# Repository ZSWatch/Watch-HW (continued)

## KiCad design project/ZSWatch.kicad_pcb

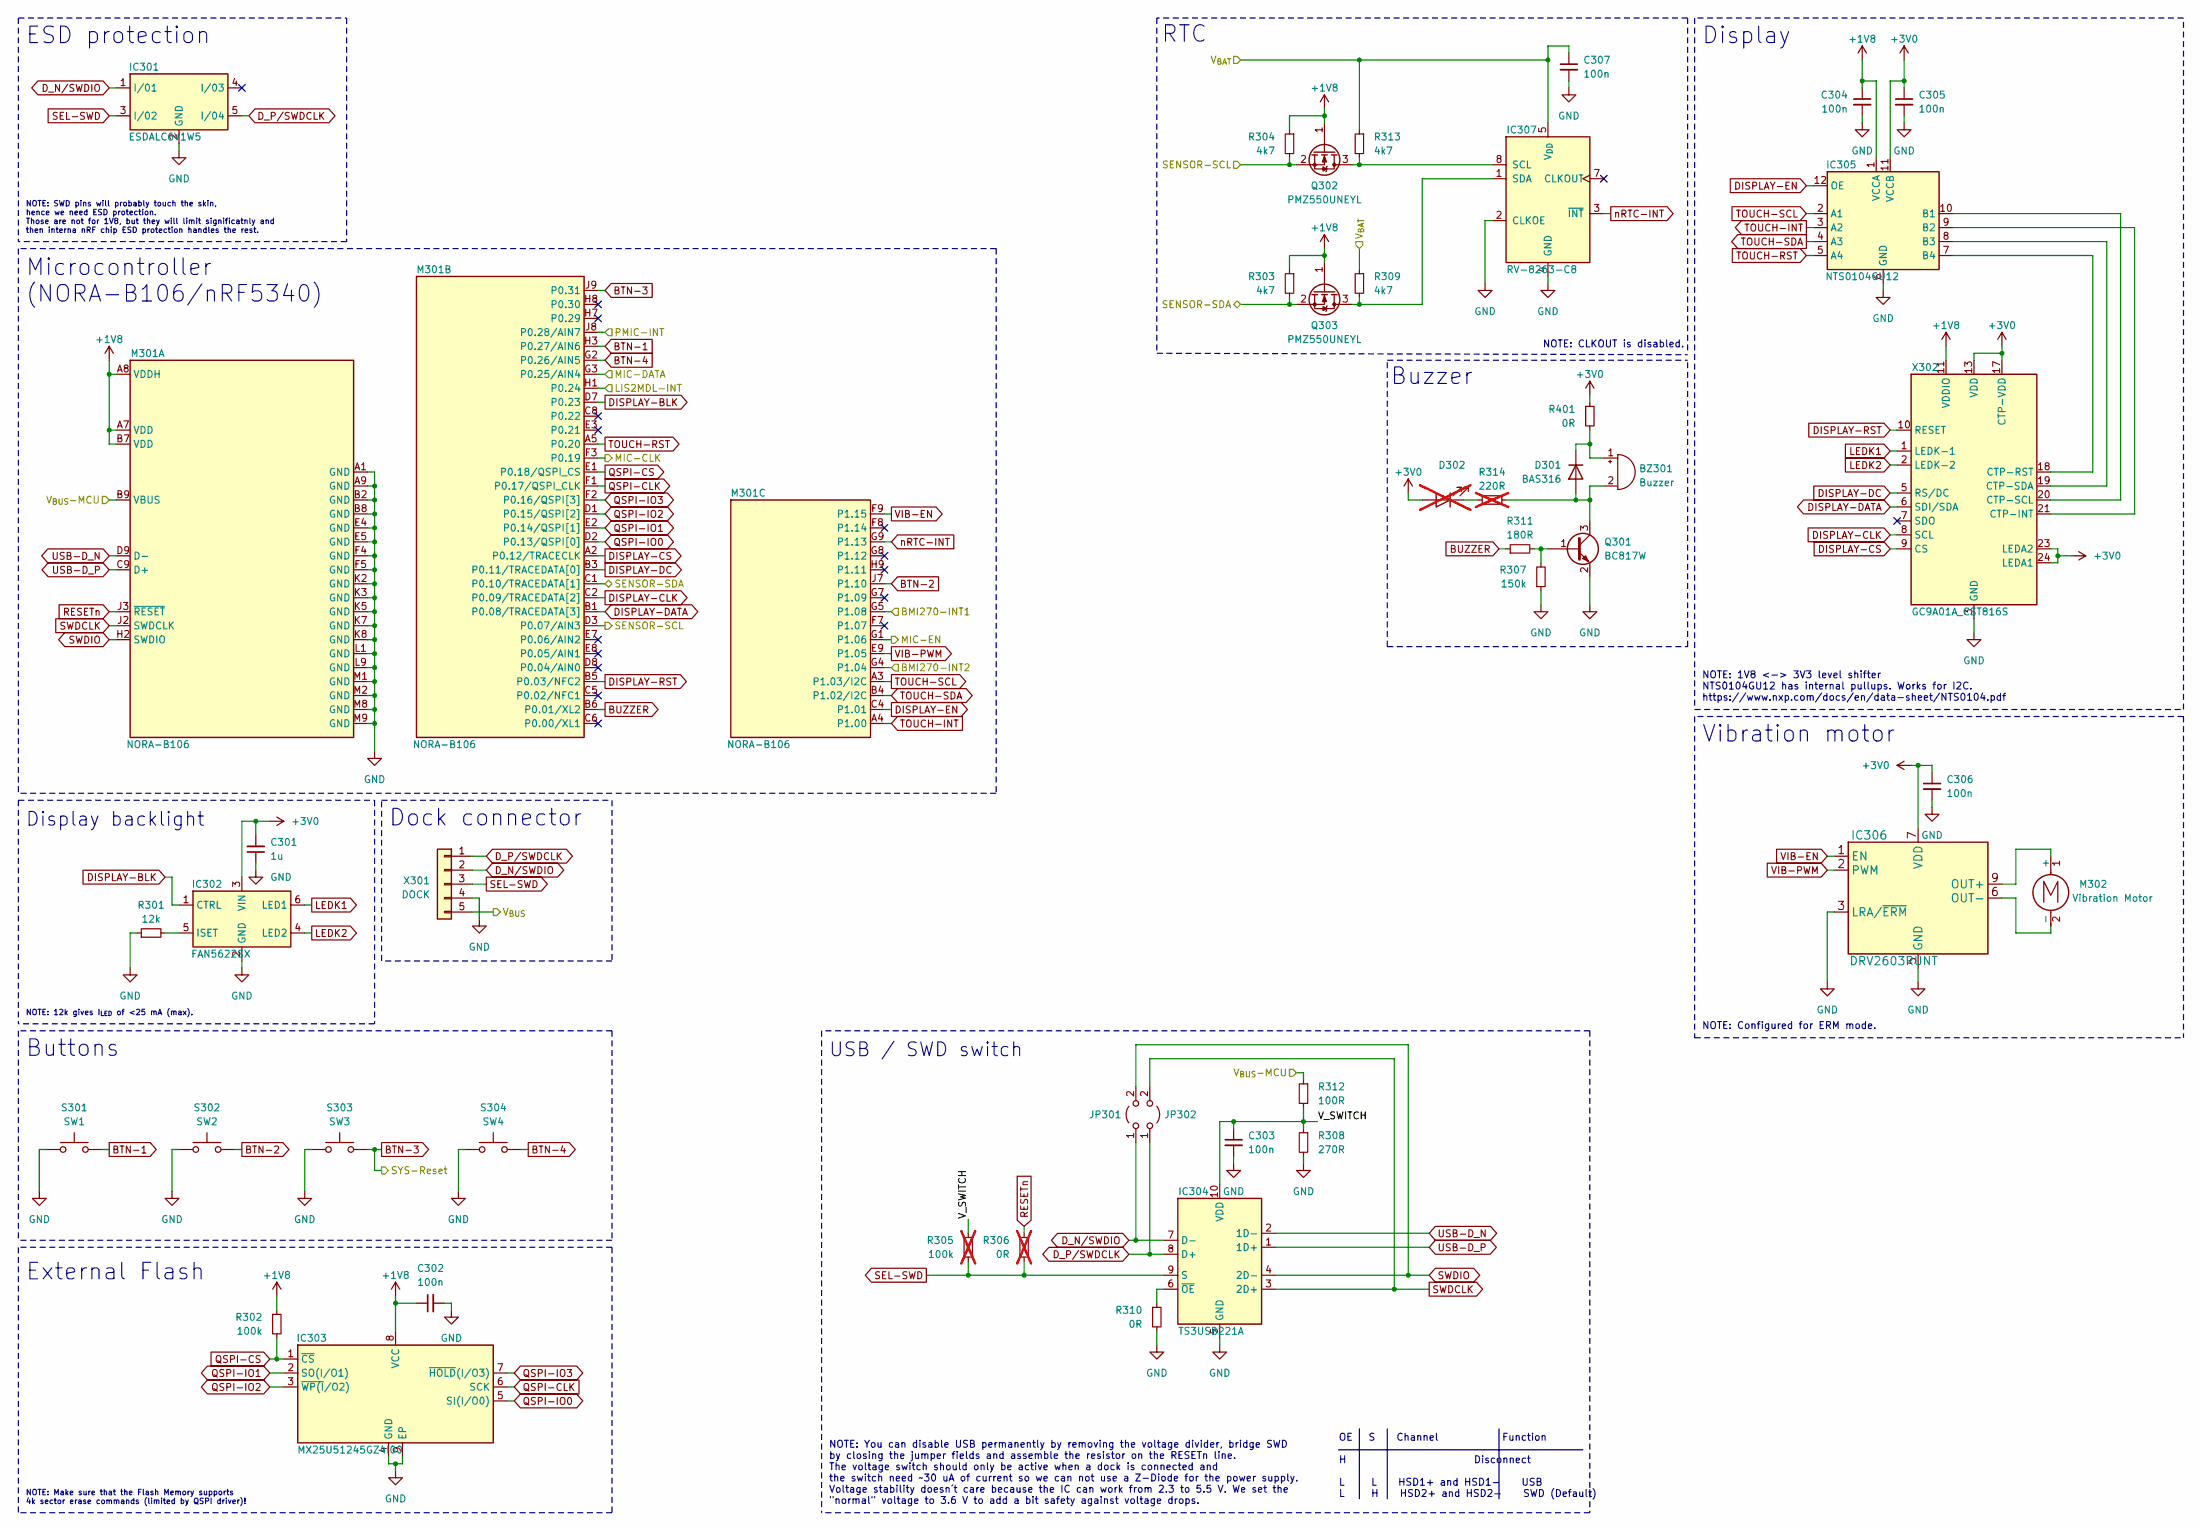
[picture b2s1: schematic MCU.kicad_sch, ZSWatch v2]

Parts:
BZ301: Buzzer; CMT-322-65-SMT-TR; mouser# 490-CMT-322-65-SMTTR
C301: 1u; C_0603_1608Metric; mouser# 581-0603YC105JAT2A
C302, C303, C304, C305, C306: 100n; C_0603_1608Metric; mouser# 581-06035C104KAT2A
C307: 100n; C_0402_1005Metric; mouser# 581-04025C104KAT2A
D301: BAS316; D_SOD-323; mouser# 821-BAS316RRG
D302: LED_0603_1608Metric; mouser# 710-150060YS75003; not fitted
IC301: ESDALC6V1W5; SOT-665; mouser# 511-ESDALC6V1P5
IC302: FAN5622SX; TSOT-23-6; mouser# 512-FAN5622SX
IC303: MX25U51245GZ4I00; WSON-8-1EP_8x6mm_P1.27mm_EP3.4x4.3mm; mouser# 95-25U51245GZ4I00T
IC304: TS3USB221A; UQFN-10_1.55x2.05mm_P0.5mm; mouser# 595-TS3USB221A
IC305: NTS0104GU12; XQFN-12-1.7x2mm_P0.4mm; mouser# 771-NTS0104GU12115
IC306: DRV2603RUNT; WQFN-10_2x2mm_P0.5mm; mouser# 595-DRV2603RUNT
IC307: RV-8263-C8; mouser# 428-204291-MC01
JP301, JP302: SolderJumper-2_P1.3mm_Open_RoundedPad1.0x1.5mm
M301: NORA-B106; mouser# 377-NORA-B106-00B
M302: Vibration Motor; VZ30C1T8219732L; mouser# 1670-VZ30C1T8219732LCT-ND
Q301: BC817W; SOT-323_SC-70; mouser# 771-BC817W115
Q302, Q303: PMZ550UNEYL; SOT-883; mouser# 771-PMZ550UNEYL
R301: 12k; R_0603_1608Metric; mouser# 603-RC0603FR-0712KL
R302: 100k; R_0603_1608Metric; mouser# 603-RC0603FR-07100KL
R303, R304: 4k7; R_0603_1608Metric; mouser# -- verschiedene Werte --
R305: 100k; R_0603_1608Metric; mouser# 603-RC0603FR-07100KL; not fitted
R306: 0R; R_0402_1005Metric; mouser# 652-CR0603-J/-000ELF; not fitted
R307: 150k; R_0603_1608Metric; mouser# 603-RC0603FR-07150KL
R308: 270R; R_0603_1608Metric; mouser# 603-RC0603FR-07270RL
R309, R313: 4k7; R_0402_1005Metric; mouser# -- verschiedene Werte --
R310: 0R; R_0402_1005Metric; mouser# 652-CR0603-J/-000ELF
R311: 180R; R_0603_1608Metric; mouser# 603-RC0603FR-07180RL
R312: 100R; R_0603_1608Metric; mouser# 603-RC0603FR-07100RL
R314: 220R; R_0603_1608Metric; mouser# 603-RT0603FRE07220RL; not fitted
R401: 0R; R_0603_1608Metric; mouser# 603-RC0603FR-100RL
S301: SW1; TL6340AF160Q_Modified; mouser# 612-TL6340AF160Q
S302: SW2; TL6340AF160Q_Modified; mouser# 612-TL6340AF160Q
S303: SW3; TL6340AF160Q_Modified; mouser# 612-TL6340AF160Q
S304: SW4; TL6340AF160Q_Modified; mouser# 612-TL6340AF160Q
X301: DOCK; RD90_LZH0230529-004_DJ-5PIN_PH2_54
X302: GC9A01A_CST816S; ER-CON0.4-24P

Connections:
+1V8: C302.1, C304.1, IC303.8 (VCC), IC305.1 (VCCA), M301.A7 (VDD), M301.A8 (VDDH), M301.B7 (VDD), Q302.1 (G), Q303.1 (G), R302.1, R303.1, R304.1, X302.11 (VDDIO), X302.12 (VDDIO); also elsewhere on the board
+3V0: C301.2, C305.1, C306.1, D302.2 (A), IC302.3 (VIN), IC305.11 (VCCB), IC306.7 (VDD), R401.1, X302.13 (VDD), X302.14 (VDD), X302.17 (CTP-VDD), X302.23 (LEDA2), X302.24 (LEDA1); also elsewhere on the board
/MCU/BMI270-INT1: M301.G5 (P1.08); also elsewhere on the board
/MCU/BMI270-INT2: M301.G4 (P1.04); also elsewhere on the board
/MCU/LIS2MDL-INT: M301.H1 (P0.24); also elsewhere on the board
/MCU/MIC-CLK: M301.F3 (P0.19); also elsewhere on the board
/MCU/MIC-DATA: M301.G3 (P0.25/AIN4); also elsewhere on the board
/MCU/MIC-EN: M301.G1 (P1.06); also elsewhere on the board
/MCU/PMIC-INT: M301.J8 (P0.28/AIN7); also elsewhere on the board
/MCU/SENSOR-SCL: M301.D3 (P0.07/AIN3), Q302.2 (S), R304.2; also elsewhere on the board
/MCU/SENSOR-SDA: M301.C1 (P0.10/TRACEDATA[1]), Q303.2 (S), R303.2; also elsewhere on the board
/MCU/V_SWITCH: C303.1, IC304.10 (VDD), R305.1, R308.1, R312.2
/MCU/V_{BAT}: C307.1, IC307.5 (V_{DD}), R309.1, R313.1; also elsewhere on the board
/MCU/V_{BUS}: X301.5; also elsewhere on the board
/MCU/V_{BUS}-MCU: M301.B9 (VBUS), R312.1; also elsewhere on the board
BTN-1: M301.H3 (P0.27/AIN6), S301.1
BTN-2: M301.J7 (P1.10), S302.2
BTN-3: M301.J9 (P0.31), S303.2; also elsewhere on the board
BTN-4: M301.G2 (P0.26/AIN5), S304.1
BUZZER: M301.B6 (P0.01/XL2), R311.1
DISPLAY-BLK: IC302.1 (CTRL), M301.D7 (P0.23)
DISPLAY-CLK: M301.C2 (P0.09/TRACEDATA[2]), X302.8 (SCL)
DISPLAY-CS: M301.A2 (P0.12/TRACECLK), X302.9 (CS)
DISPLAY-DATA: M301.B1 (P0.08/TRACEDATA[3]), X302.6 (SDI/SDA)
DISPLAY-DC: M301.B3 (P0.11/TRACEDATA[0]), X302.5 (RS/DC)
DISPLAY-EN: IC305.12 (OE), M301.C4 (P1.01)
DISPLAY-RST: M301.B5 (P0.03/NFC2), X302.10 (RESET)
D_N/SWDIO: IC301.1 (I/01), IC304.7 (D-), JP301.1 (A), X301.2
D_P/SWDCLK: IC301.5 (I/04), IC304.8 (D+), JP302.1 (A), X301.1
GND: C301.1, C302.2, C303.2, C304.2, C305.2, C306.2, C307.2, IC301.2 (GND), IC302.2 (GND), IC303.4 (GND), IC303.9 (EP), IC304.5 (GND), IC305.6 (GND), IC306.3 (LRA/~ERM), IC306.5 (GND), IC306.8 (GND), IC306.10 (GND), IC307.2 (CLKOE), IC307.4 (GND), M301.A1 (GND), M301.A9 (GND), M301.B2 (GND), M301.B8 (GND), M301.E4 (GND), M301.E5 (GND), M301.F4 (GND), M301.F5 (GND), M301.K2 (GND), M301.K3 (GND), M301.K5 (GND), M301.K7 (GND), M301.K8 (GND), M301.L1 (GND), M301.L9 (GND), M301.M1 (GND), M301.M2 (GND), M301.M8 (GND), M301.M9 (GND), Q301.2 (E), R301.1, R307.1, R308.2, R310.2, S301.2, S302.1, S303.1, S304.2, X301.4, X302.3 (GND), X302.4 (GND), X302.15 (GND), X302.16 (GND); also elsewhere on the board
LEDK1: IC302.6 (LED1), X302.1 (LEDK-1)
LEDK2: IC302.4 (LED2), X302.2 (LEDK-2)
unnamed: BZ301.1 (+), D301.1 (K), R401.2
unnamed: BZ301.2 (-), D301.2 (A), Q301.3 (C), R314.2
unnamed: D302.1 (K), R314.1
unnamed: IC302.5 (ISET), R301.2
unnamed: IC304.6 (~OE), R310.1
unnamed: IC305.10 (B1), X302.20 (CTP-SCL)
unnamed: IC305.9 (B2), X302.21 (CTP-INT)
unnamed: IC305.8 (B3), X302.19 (CTP-SDA)
unnamed: IC305.7 (B4), X302.18 (CTP-RST)
unnamed: IC306.9 (OUT+), M302.1 (+)
unnamed: IC306.6 (OUT-), M302.2 (-)
unnamed: IC307.8 (SCL), Q302.3 (D), R313.2
unnamed: IC307.1 (SDA), Q303.3 (D), R309.2
unnamed: Q301.1 (B), R307.2, R311.2
QSPI-CLK: IC303.6 (SCK), M301.F1 (P0.17/QSPI_CLK)
QSPI-CS: IC303.1 (~CS), M301.E1 (P0.18/QSPI_CS), R302.2
QSPI-IO0: IC303.5 (SI(I/O0)), M301.D2 (P0.13/QSPI[0])
QSPI-IO1: IC303.2 (SO(I/O1)), M301.E2 (P0.14/QSPI[1])
QSPI-IO2: IC303.3 (~WP(I/O2)), M301.D1 (P0.15/QSPI[2])
QSPI-IO3: IC303.7 (~HOLD(I/O3)), M301.F2 (P0.16/QSPI[3])
RESETn: M301.J3 (~RESET), R306.2
SEL-SWD: IC301.3 (I/02), IC304.9 (S), R305.2, R306.1, X301.3
SWDCLK: IC304.3 (2D+), JP302.2 (B), M301.J2 (SWDCLK)
SWDIO: IC304.4 (2D-), JP301.2 (B), M301.H2 (SWDIO)
TOUCH-INT: IC305.3 (A2), M301.A4 (P1.00)
TOUCH-RST: IC305.5 (A4), M301.A5 (P0.20)
TOUCH-SCL: IC305.2 (A1), M301.A3 (P1.03/I2C)
TOUCH-SDA: IC305.4 (A3), M301.B4 (P1.02/I2C)
USB-D_N: IC304.2 (1D-), M301.D9 (D-)
USB-D_P: IC304.1 (1D+), M301.C9 (D+)
VIB-EN: IC306.1 (EN), M301.F9 (P1.15)
VIB-PWM: IC306.2 (PWM), M301.E9 (P1.05)
nRTC-INT: IC307.3 (~INT), M301.G9 (P1.13)

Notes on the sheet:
NOTE: CLKOUT is disabled.
OE S Channel Function H Disconnect L L HSD1+ and HSD1- USB L H HSD2+ and HSD2- SWD (Default)
Buttons
NOTE: 12k gives I_{LED} of <25 mA (max).
Vibration motor
Buzzer
NOTE: Make sure that the Flash Memory supports 4k sector erase commands (limited by QSPI driver)!
NOTE: SWD pins will probably touch the skin, hence we need ESD protection. Those are not for 1V8, but they will limit significatnly and then interna nRF chip ESD protection handles the rest.
USB / SWD switch
RTC
Display
NOTE: 1V8 <-> 3V3 level shifter NTS0104GU12 has internal pullups. Works for I2C. https://www.nxp.com/docs/en/data-sheet/NTS0104.pdf
NOTE: You can disable USB permanently by removing the voltage divider, bridge SWD by closing the jumper fields and assemble the resistor on the RESETn line. The voltage switch should only be active when a dock is connected and the switch need ~30 uA of current so we can not use a Z-Diode for the po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
Microcontroller (NORA-B106/nRF5340)
Display backlight
NOTE: Configured for ERM mode.
Dock connector
External Flash
ESD protection

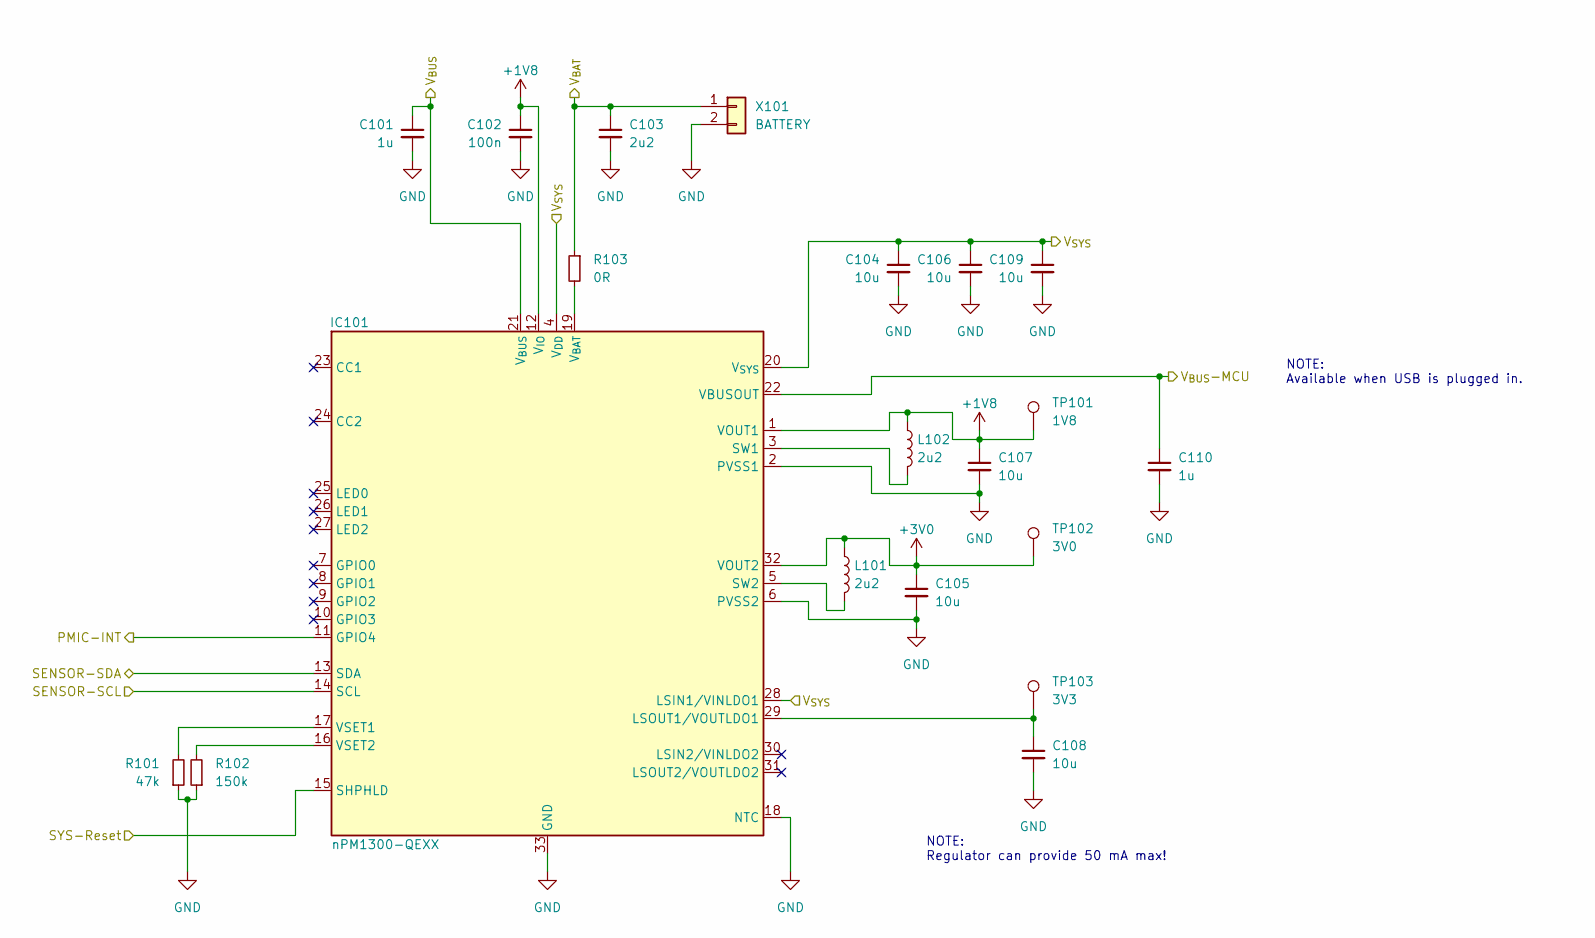
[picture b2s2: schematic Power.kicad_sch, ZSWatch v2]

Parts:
C101, C110: 1u; C_0603_1608Metric; mouser# 581-0603YC105JAT2A
C102: 100n; C_0603_1608Metric; mouser# 581-06035C104KAT2A
C103: 2u2; C_0603_1608Metric; mouser# 581-06036D225KAT2A
C104, C105, C106, C107, C108, C109: 10u; C_0603_1608Metric; mouser# 346-CM105X5R106M25AT
IC101: nPM1300-QEXX; QFN-32-1EP_5x5mm_P0.5mm_EP3.6x3.6mm; mouser# 949-NPM1300-QEAA-R7
L101, L102: 2u2; L_0806_2016; mouser# 187-CIGT201610EH2R2MNE
R101: 47k; R_0603_1608Metric; mouser# 603-RC0603FR-0747KL
R102: 150k; R_0603_1608Metric; mouser# 603-RC0603FR-07150KL
R103: 0R; R_0402_1005Metric; mouser# 652-CR0603-J/-000ELF
TP101: 1V8; TestPoint_Pad_D1.0mm
TP102: 3V0; TestPoint_Pad_D1.0mm
TP103: 3V3; TestPoint_Pad_D1.0mm
X101: BATTERY; 78171-0002; mouser# 538-78171-0002

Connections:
+1V8: C102.1, C107.1, IC101.1 (VOUT1), IC101.12 (V_{IO}), L102.1, TP101.1; also elsewhere on the board
+3V0: C105.1, IC101.32 (VOUT2), L101.1, TP102.1; also elsewhere on the board
/MCU/PMIC-INT: IC101.11 (GPIO4); also elsewhere on the board
/MCU/SENSOR-SCL: IC101.14 (SCL); also elsewhere on the board
/MCU/SENSOR-SDA: IC101.13 (SDA); also elsewhere on the board
/MCU/V_{BAT}: C103.1, R103.1, X101.1; also elsewhere on the board
/MCU/V_{BUS}: C101.1, IC101.21 (V_{BUS}); also elsewhere on the board
/MCU/V_{BUS}-MCU: C110.1, IC101.22 (VBUSOUT); also elsewhere on the board
/Power Management/V_{SYS}: C104.1, C106.1, C109.1, IC101.4 (V_{DD}), IC101.20 (V_{SYS}), IC101.28 (LSIN1/VINLDO1)
BTN-3: IC101.15 (SHPHLD); also elsewhere on the board
GND: C101.2, C102.2, C103.2, C104.2, C105.2, C106.2, C107.2, C108.2, C109.2, C110.2, IC101.2 (PVSS1), IC101.6 (PVSS2), IC101.18 (NTC), IC101.33 (GND), R101.1, R102.1, X101.2; also elsewhere on the board
unnamed: C108.1, IC101.29 (LSOUT1/VOUTLDO1), TP103.1
unnamed: IC101.3 (SW1), L102.2
unnamed: IC101.5 (SW2), L101.2
unnamed: IC101.17 (VSET1), R101.2
unnamed: IC101.16 (VSET2), R102.2
unnamed: IC101.19 (V_{BAT}), R103.2

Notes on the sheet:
NOTE: Available when USB is plugged in.
NOTE: Regulator can provide 50 mA max!

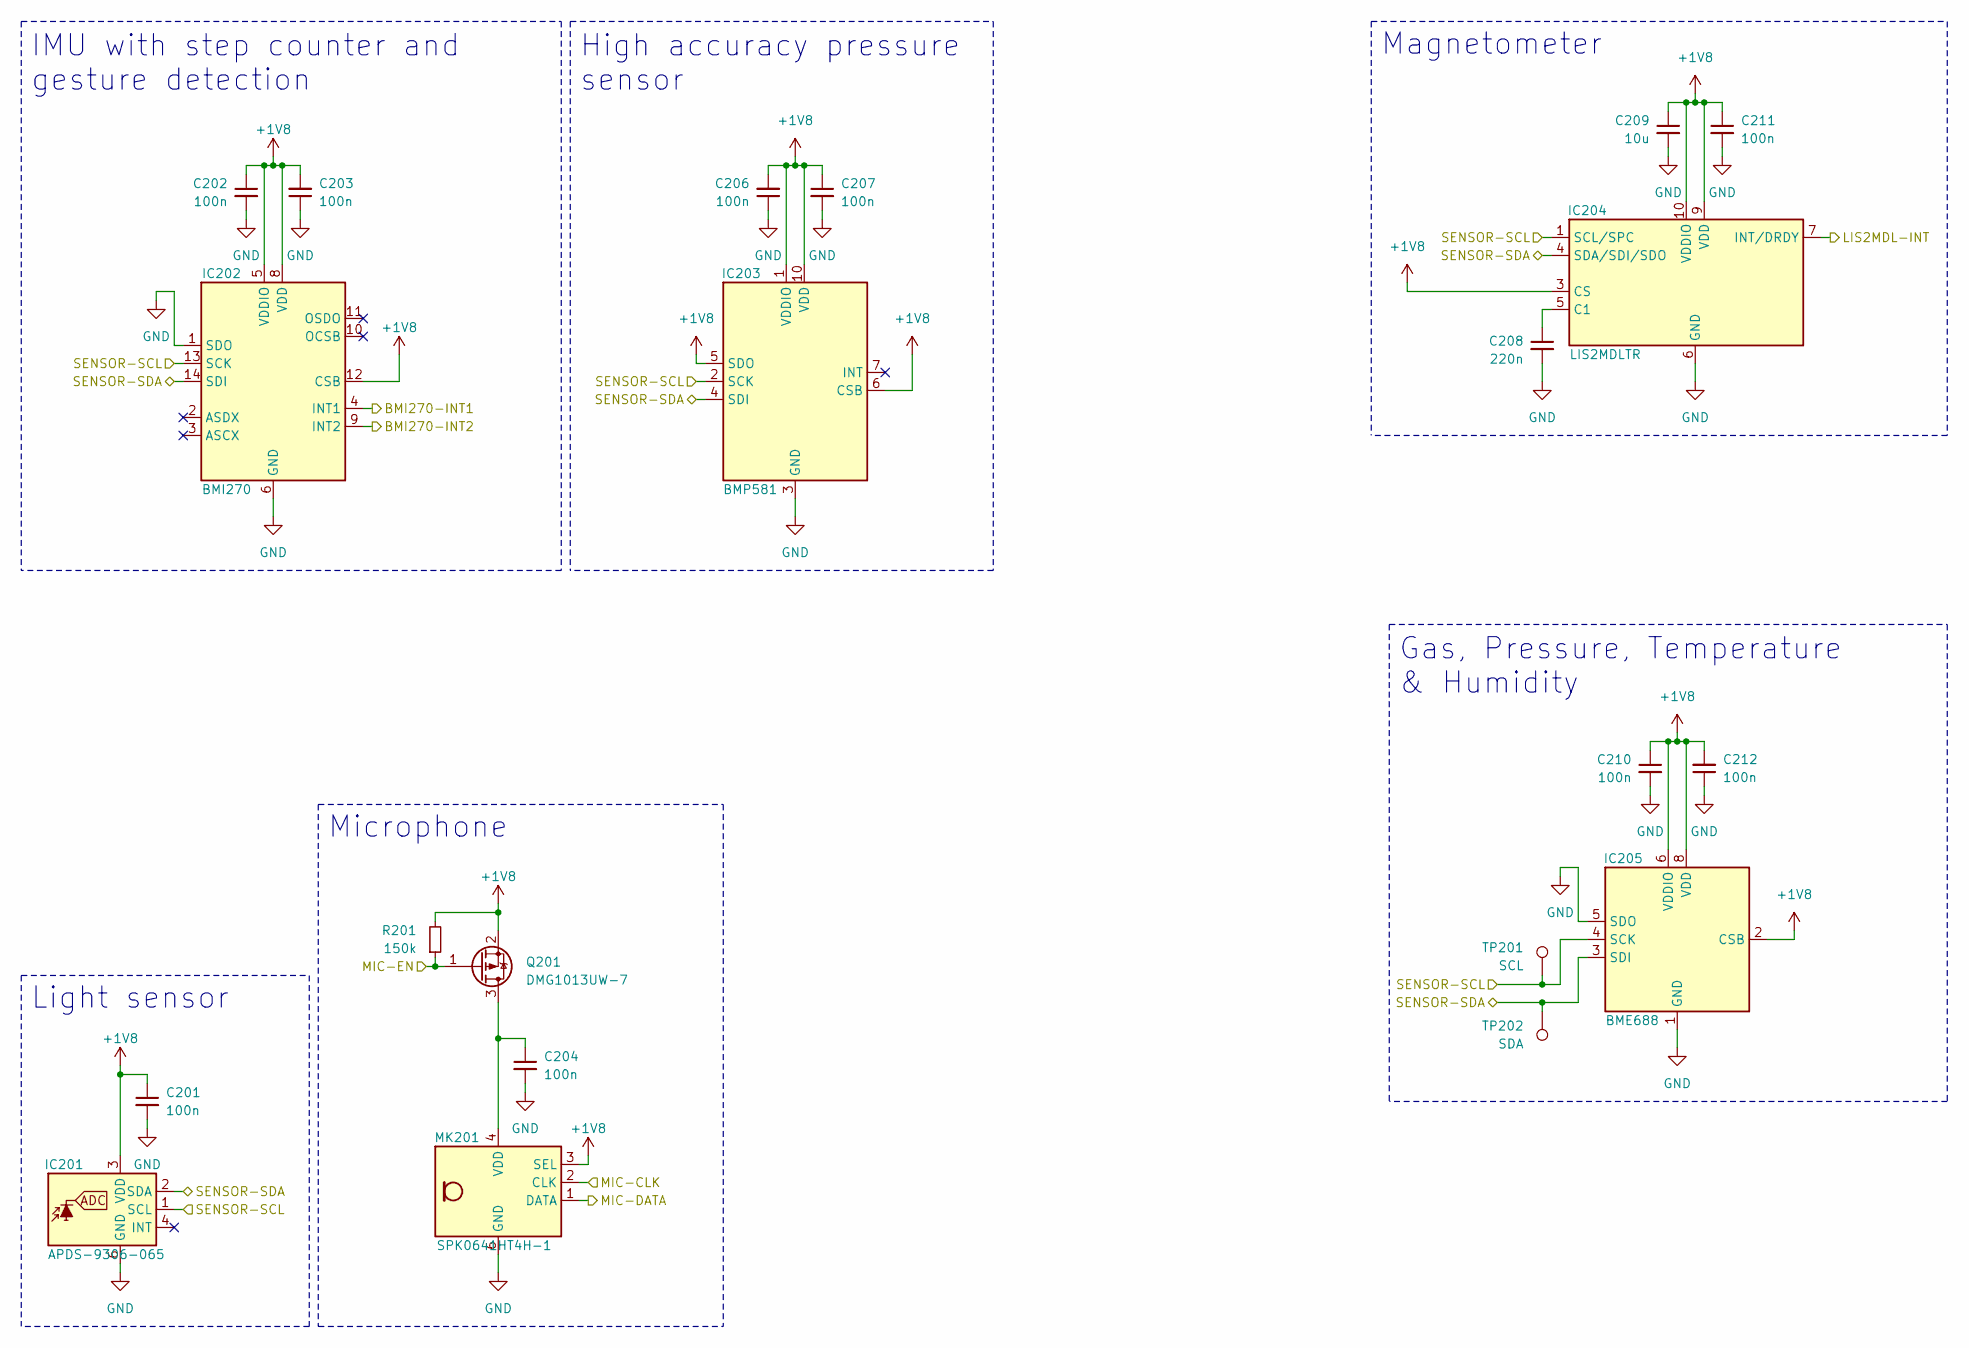
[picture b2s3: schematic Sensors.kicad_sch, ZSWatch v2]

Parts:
C201, C202, C203, C204, C206, C207, C210, C211, C212: 100n; C_0603_1608Metric; mouser# 581-06035C104KAT2A
C208: 220n; C_0603_1608Metric; mouser# 581-06033C224KAT2A
C209: 10u; C_0603_1608Metric; mouser# 346-CM105X5R106M25AT
IC201: APDS-9306-065; Broadcom_DFN-6_2x2mm_P0.65mm; mouser# 630-APDS-9306-065
IC202: BMI270; Bosch_LGA-14_3x2.5mm_P0.5mm_LayoutBorder3x4y; mouser# 262-BMI270
IC203: BMP581; Bosch_LGA-10_2x2mm_P0.5mm_ClockwisePinNumbering; mouser# 262-BMP581
IC204: LIS2MDLTR; LGA-12_2x2mm_P0.5mm; mouser# 511-LIS2MDLTR
IC205: BME688; Bosch_LGA-8_3x3mm_P0.8mm_ClockwisePinNumbering; mouser# 262-BME688
MK201: SPK0641HT4H-1; mouser# 721-SPK0641HT4H-1
Q201: DMG1013UW-7; SOT-323_SC-70; mouser# 621-DMG1013UW-7
R201: 150k; R_0603_1608Metric; mouser# 603-RC0603FR-07150KL
TP201: SCL; TestPoint_Pad_D1.0mm
TP202: SDA; TestPoint_Pad_D1.0mm

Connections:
+1V8: C201.1, C202.1, C203.2, C206.2, C207.1, C209.1, C210.1, C211.1, C212.2, IC201.3 (VDD), IC202.5 (VDDIO), IC202.8 (VDD), IC202.12 (CSB), IC203.1 (VDDIO), IC203.5 (SDO), IC203.6 (CSB), IC203.10 (VDD), IC204.3 (CS), IC204.9 (VDD), IC204.10 (VDDIO), IC205.2 (CSB), IC205.6 (VDDIO), IC205.8 (VDD), MK201.3 (SEL), Q201.2 (S), R201.2; also elsewhere on the board
/MCU/BMI270-INT1: IC202.4 (INT1); also elsewhere on the board
/MCU/BMI270-INT2: IC202.9 (INT2); also elsewhere on the board
/MCU/LIS2MDL-INT: IC204.7 (INT/DRDY); also elsewhere on the board
/MCU/MIC-CLK: MK201.2 (CLK); also elsewhere on the board
/MCU/MIC-DATA: MK201.1 (DATA); also elsewhere on the board
/MCU/MIC-EN: Q201.1 (G), R201.1; also elsewhere on the board
/MCU/SENSOR-SCL: IC201.1 (SCL), IC202.13 (SCK), IC203.2 (SCK), IC204.1 (SCL/SPC), IC205.4 (SCK), TP201.1; also elsewhere on the board
/MCU/SENSOR-SDA: IC201.2 (SDA), IC202.14 (SDI), IC203.4 (SDI), IC204.4 (SDA/SDI/SDO), IC205.3 (SDI), TP202.1; also elsewhere on the board
GND: C201.2, C202.2, C203.1, C204.2, C206.1, C207.2, C208.2, C209.2, C210.2, C211.2, C212.1, IC201.6 (GND), IC202.1 (SDO), IC202.6 (GND), IC202.7 (GND), IC203.3 (GND), IC203.8 (GND), IC203.9 (GND), IC204.6 (GND), IC204.8 (GND), IC205.1 (GND), IC205.5 (SDO), IC205.7 (GND), MK201.5 (GND), MK201.6 (GND), MK201.7 (GND), MK201.8 (GND); also elsewhere on the board
unnamed: C208.1, IC204.5 (C1)
unnamed: C204.1, MK201.4 (VDD), Q201.3 (D)

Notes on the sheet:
Gas, Pressure, Temperature & Humidity
Magnetometer
High accuracy pressure sensor
Microphone
Light sensor
IMU with step counter and gesture detection

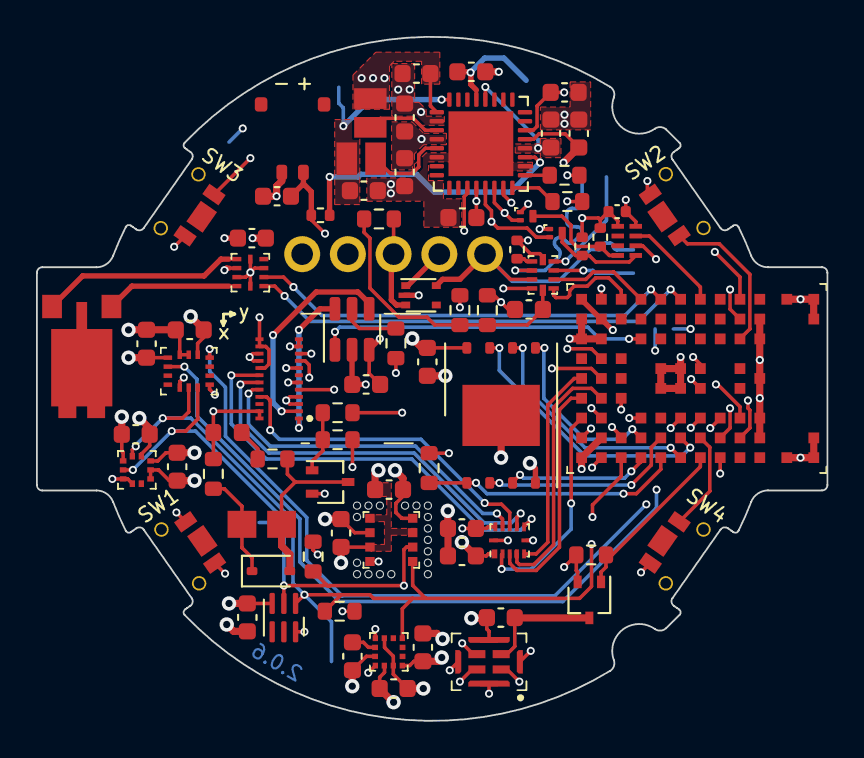
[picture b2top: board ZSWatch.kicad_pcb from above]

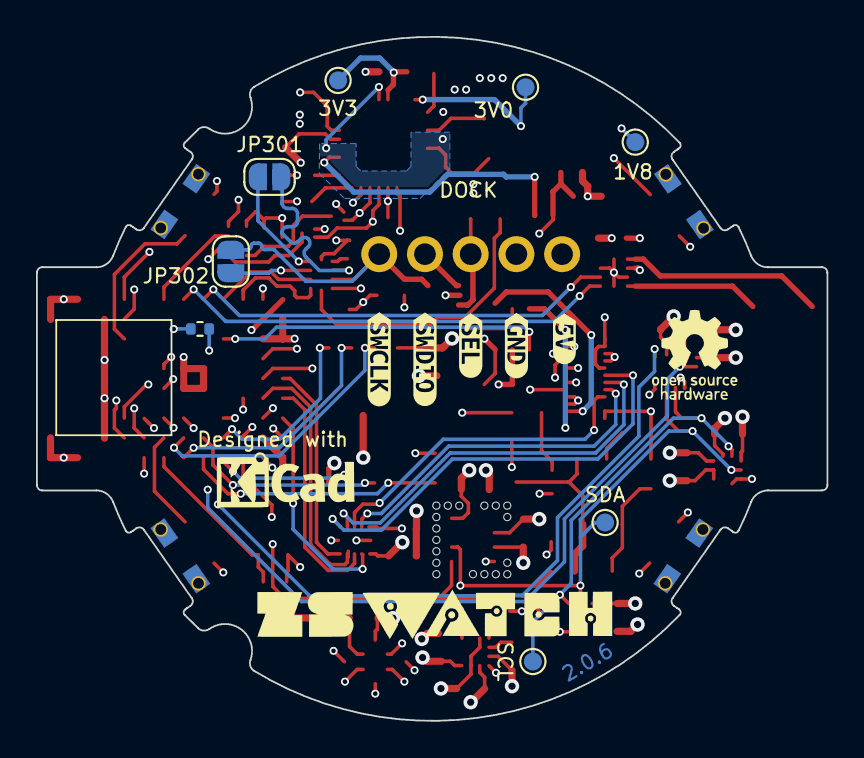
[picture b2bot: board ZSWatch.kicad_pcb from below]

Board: 4 copper layers, 43.9 x 38.0 mm, 91 parts (14 on the bottom side), 74 nets.

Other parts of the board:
kibuzzard-6616D313: G***; kibuzzard-6616D313
kibuzzard-656642B5: G***; kibuzzard-656642B5
kibuzzard-656642E4: G***; kibuzzard-656642E4
kibuzzard-65664337: G***; kibuzzard-65664337
kibuzzard-65664342: G***; kibuzzard-65664342

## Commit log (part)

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2024-12-30 Add KiCost
2025-01-02 Fix wrong part numbers
2025-01-02 Add image from CI/CD action
2025-01-03 Rebase with upstream 2.0.6
2025-04-06 Fix ci issue.
2025-12-13 Initialize repository
2025-12-13 First prototype release ready
2025-12-22 Add speaker
2026-02-01 New PCB outline, fix logo copy job for KiBot
2026-02-02 Move display connector 3 mm to the outside and optimize routing
2026-02-06 Fix wrong Extension footprint
2026-02-10 New buttons
2026-02-18 New battery connector
    - Add CI/CD workflow to check for changelog updates on pull requests
2026-02-18 Replace wrong extension connectors
2026-02-19 OPtimize connector positions
    - New position for the battery connector, moved to the right side of the watch
    - Rotate haptics connector by 180°
2026-02-19 Rename PCB workflow, add part number for battery connector, remove sim pins property
2026-02-20 Prepare release 1.0.0
2026-02-20 Push outputs from CI/CD (2026-02-20 15:45:10)
2026-02-20 Release 1.0.0
2026-02-20 Push outputs from CI/CD (2026-02-20 19:25:28)
2026-02-21 Update CHANGELOG
2026-02-21 Update outputs (release)
2026-04-17 Update README with prototype warnings and links
    Added important notes regarding the prototype status and ordering recommendations.
